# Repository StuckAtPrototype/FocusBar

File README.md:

# FocusBar

A compact Pomodoro timer device with visual LED progress bar, tactile button controls, and audio feedback. Designed to help you stay focused and productive.

## Features

- **Visual Progress Bar**: 10 WS2812 addressable RGB LEDs show timer progress
- **5 Preset Durations**: Quick-select buttons for 5, 15, 30, 45, and 60 minute focus sessions
- **Audio Feedback**: Piezo buzzer for startup jingle, completion notification, and alert sounds
- **Intuitive States**: Color-coded LED feedback for different timer states
- **USB-C Powered**: Modern, reversible connector for easy power
- **Compact Design**: Custom PCB with 3D-printable enclosure

## Timer States

| State | LED Color | Behavior |
|-------|-----------|----------|
| Idle | Cyan (30% brightness) | All LEDs solid, ready to start |
| Running | Green | Progress bar fills from 0-100% |
| Completed | Green (pulsing) | 60-second grace period to acknowledge |
| Alerting | Red (pulsing) | Audio alert every 2 seconds until dismissed |

## Usage

1. **Start Timer**: Press any of the 5 buttons to start the corresponding timer:
   - Button 1: 5 minutes
   - Button 2: 15 minutes
   - Button 3: 30 minutes
   - Button 4: 45 minutes
   - Button 5: 60 minutes

2. **Cancel Timer**: Press any button while timer is running to stop and reset

3. **Acknowledge Completion**: Press any button during the grace period (green pulsing) to reset without triggering the alert

4. **Dismiss Alert**: Press any button during the alert (red pulsing) to silence and reset

## Hardware

### Components

| Component | Part Number | Description |
|-----------|-------------|-------------|
| MCU | ESP32-H2-MINI-1 | WiFi/BLE microcontroller module |
| LEDs | IN-PI15TAT5R5G5B | WS2812-compatible addressable RGB LEDs (x10) |
| Buttons | TL1016AAF220QG | Tactile push buttons (x5) |
| Buzzer | SMT1240SHT | SMD piezo buzzer |
| Regulator | AP2205-33W5-7 | 3.3V LDO voltage regulator |
| USB | USB4105-GF-A | USB-C connector |
| ESD Protection | TPD1E10B06 | USB ESD protection diode |

### PCB

- **Design Tool**: KiCad
- **Files Location**: `hardware/`
- **Schematic**: `FocusBeam.kicad_sch`
- **PCB Layout**: `FocusBeam.kicad_pcb`
- **Gerbers**: `gerbers/` or `FocusBeam-v1.1-fab-gerbers.zip`
- **BOM**: `FocusBeam-v1.1-BOM.csv`
- **Panel Design**: `panel/` (for production runs)

### Mechanical

3D-printable enclosure files (STEP format) located in `mechanical/`:
- `FocusBeam_v1.1_front.step` - Front cover
- `FocusBeam_v1.1_back.step` - Back cover
- `FocusBeam_v1.1_buttons.step` - Button caps
- `FocusBeam_v.1.1_stand.step` - Desktop stand

## Firmware

### Requirements

- [ESP-IDF](https://docs.espressif.com/projects/esp-idf/en/latest/esp32h2/get-started/index.html) v5.x or later
- ESP32-H2 target support

### Building

```bash
cd firmware
idf.py set-target esp32h2
idf.py build
```

### Flashing

```bash
idf.py -p (PORT) flash monitor
```

Replace `(PORT)` with your serial port (e.g., `COM3` on Windows, `/dev/ttyUSB0` on Linux).

### Firmware Architecture

```
firmware/
├── CMakeLists.txt          # Project build configuration
├── sdkconfig.ci            # SDK configuration
└── main/
    ├── main.c              # Application entry point and main loop
    ├── button.c/h          # Button input handling (short/long press)
    ├── led.c/h             # LED control (colors, progress, pulsing)
    ├── led_color_lib.c/h   # Color utilities
    ├── piezo.c/h           # Buzzer control (tones, melodies)
    ├── timer.c/h           # Pomodoro state machine
    ├── serial_protocol.c/h # Serial communication (future use)
    └── ws2812_control.c/h  # WS2812 LED driver (RMT peripheral)
```

### Key Modules

- **Timer**: State machine managing idle, running, completed, grace period, and alerting states
- **LED**: Thread-safe LED control with smooth transitions and pulsing effects
- **Button**: Interrupt-driven button handler with debouncing and short/long press detection
- **Piezo**: PWM-based buzzer control for tones and melodies

## Pin Configuration

| Function | GPIO |
|----------|------|
| WS2812 Data | (see ws2812_control.c) |
| Button SW0 | GPIO 10 |
| Button SW1 | GPIO 5 |
| Button SW2 | GPIO 4 |
| Button SW3 | GPIO 14 |
| Button SW4 | GPIO 13 |
| Piezo | GPIO 22 |

## Project Structure

```
FocusBar/
├── README.md               # This file
├── firmware/               # ESP-IDF firmware project
│   ├── main/               # Source code
│   └── CMakeLists.txt
├── hardware/               # KiCad PCB design files
│   ├── FocusBeam.kicad_*   # Main PCB files
│   ├── gerbers/            # Manufacturing files
│   ├── panel/              # Panelized PCB for production
│   └── FocusBeam.step      # 3D model of PCB
└── mechanical/             # 3D-printable enclosure (STEP files)
```

## License

Licensed under the Apache License, Version 2.0. See [LICENSE](LICENSE) for details.

## Author

StuckAtPrototype, LLC

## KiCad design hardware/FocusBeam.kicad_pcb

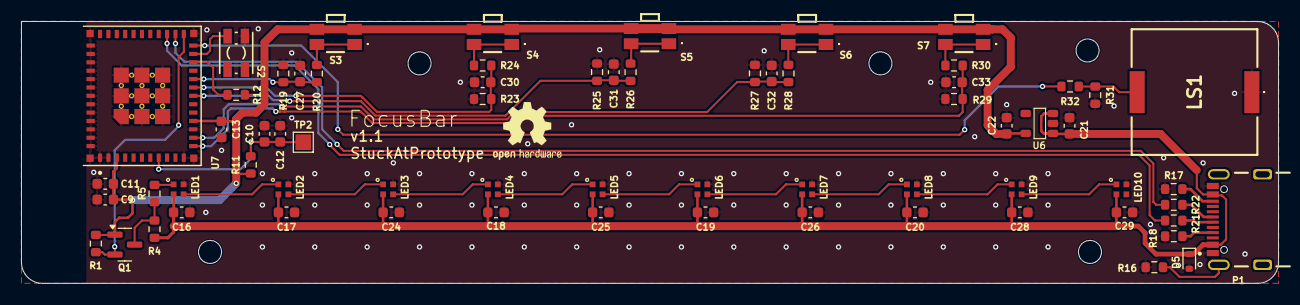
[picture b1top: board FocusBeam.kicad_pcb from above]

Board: 2 copper layers, 120.0 x 25.0 mm, 67 parts (0 on the bottom side), 37 nets.

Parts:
C9: 47uF; C_0603_1608Metric
C10: 1uF; C_0603_1608Metric
C11, C12, C13, C16, C17, C18, C19, C20, C24, C25, C26, C27, C28, C29, C30, C31, C32, C33: 0.1uF; C_0603_1608Metric
C21, C22: 10uF; C_0603_1608Metric
D5: TPD1E10B06; D_SOD-523
LED1, LED2, LED3, LED4, LED5, LED6, LED7, LED8, LED9, LED10: IN-PI15TAT5R5G5B; IN-PI15_INL
LS1: SMT1240SHT
P1: USB_C_Plug_USB2.0; GCT_USB4105-GF-A
Q1: BSS138; SOT-23
R1, R4, R11, R12: 10K; R_0603_1608Metric
R5: 470; R_0603_1608Metric
R16, R31: 1M; R_0603_1608Metric
R17, R18: 5K1; R_0603_1608Metric
R19, R23, R25, R27, R29: 100k; R_0603_1608Metric
R20, R24, R26, R28, R30: 10k; R_0603_1608Metric
R21, R22: 22; R_0603_1608Metric
R32: 100; R_0603_1608Metric
S2: SWITCH_0SMTRLFS
S3, S4, S5, S6, S7: TL1016AAF220QG
TP2: TestPoint; TestPoint_Pad_1.5x1.5mm
U6: AP2205; AP2204
U7: ESP32-H2-MINI-1; MODULE_ESP32-H2-MINI-1-H2

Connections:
+3V3: C9.1, C11.1, C13.1, C22.1, Q1.1 (G), R1.2, R11.1, R12.2, S3.3, S3.4, S4.3, S4.4, S5.3, S5.4, S6.3, S6.4, S7.3, S7.4, U6.5 (VOUT), U7.3 (3v3), U7.15 (VBAT)
+5VD: C16.1, C17.1, C18.1, C19.1, C20.1, C21.1, C24.1, C25.1, C26.1, C28.1, C29.1, D5.1, LED1.2 (VDD), LED2.2 (VDD), LED3.2 (VDD), LED4.2 (VDD), LED5.2 (VDD), LED6.2 (VDD), LED7.2 (VDD), LED8.2 (VDD), LED9.2 (VDD), LED10.2 (VDD), P1.A4 (VBUS), P1.A9 (VBUS), R4.2, U6.1 (VIN), U6.3 (EN)
/CP_EN: C10.1, C12.1, R11.2, TP2.1, U7.8 (EN)
/SW_0: C27.1, R19.1, R20.1, U7.20 (IO10)
/SW_1: C30.1, R23.1, R24.1, U7.19 (IO5)
/SW_2: C31.1, R25.1, R26.1, U7.18 (IO4)
/SW_3: C32.1, R27.1, R28.1, U7.13 (IO14)
/SW_4: C33.1, R29.1, R30.1, U7.12 (IO13)
/USB_D+: R21.1, U7.27 (IO27)
/USB_D-: R22.2, U7.26 (IO26)
GND: C9.2, C10.2, C11.2, C12.2, C13.2, C16.2, C17.2, C18.2, C19.2, C20.2, C21.2, C22.2, C24.2, C25.2, C26.2, C27.2, C28.2, C29.2, C30.2, C31.2, C32.2, C33.2, D5.2, LED1.4 (GND), LED2.4 (GND), LED3.4 (GND), LED4.4 (GND), LED5.4 (GND), LED6.4 (GND), LED7.4 (GND), LED8.4 (GND), LED9.4 (GND), LED10.4 (GND), LS1.1, P1.A1 (GND), P1.A12 (GND), R16.2, R17.2, R18.2, R19.2, R23.2, R25.2, R27.2, R29.2, R31.2, S2.1, U6.2 (GND), U7.1 (GND), U7.2 (GND), U7.11 (GND), U7.14 (GND), U7.36 (GND), U7.37 (GND), U7.38 (GND), U7.39 (GND), U7.40 (GND), U7.41 (GND), U7.42 (GND), U7.43 (GND), U7.44 (GND), U7.45 (GND), U7.46 (GND), U7.47 (GND), U7.48 (GND), U7.49 (EPAD), U7.50 (GND), U7.51 (GND), U7.52 (GND), U7.53 (GND)
unnamed: LED1.1 (DIN), R5.2
unnamed: LED1.3 (DOUT), LED2.1 (DIN)
unnamed: LED2.3 (DOUT), LED3.1 (DIN)
unnamed: LED3.3 (DOUT), LED4.1 (DIN)
unnamed: LED4.3 (DOUT), LED5.1 (DIN)
unnamed: LED5.3 (DOUT), LED6.1 (DIN)
unnamed: LED6.3 (DOUT), LED7.1 (DIN)
unnamed: LED7.3 (DOUT), LED8.1 (DIN)
unnamed: LED8.3 (DOUT), LED9.1 (DIN)
unnamed: LED9.3 (DOUT), LED10.1 (DIN)
unnamed: LS1.2, R31.1, R32.1
unnamed: P1.A5 (CC), R18.1
unnamed: P1.A6 (D+), R21.2
unnamed: P1.A7 (D-), R22.1
unnamed: P1.S1 (SHIELD), R16.1
unnamed: P1.B5 (VCONN), R17.1
unnamed: Q1.3 (D), R4.1, R5.1
unnamed: Q1.2 (S), R1.1, U7.25 (IO25)
unnamed: R20.2, S3.1, S3.2
unnamed: R24.2, S4.1, S4.2
unnamed: R26.2, S5.1, S5.2
unnamed: R28.2, S6.1, S6.2
unnamed: R30.2, S7.1, S7.2
unnamed: R12.1, U7.22 (IO08)
unnamed: S2.2, U7.23 (IO9)
unnamed: R32.2, U7.24 (IO22)

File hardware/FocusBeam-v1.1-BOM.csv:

Id,Designator,Footprint,Quantity,Designation,Supplier and ref
1,"C32,C26,C28,C12,C19,C31,C20,C24,C16,C33,C17,C27,C11,C30,C13,C25,C18,C29",C_0603_1608Metric,18,0.1uF,CC0603KRX7R7BB104
2,R5,R_0603_1608Metric,1,470,ESR03EZPF4700
3,"R25,R29,R19,R23,R27",R_0603_1608Metric,5,100k,WR06X1003FTL
4,"LED2,LED3,LED9,LED8,LED1,LED6,LED4,LED7,LED5,LED10",IN-PI15_INL,10,IN-PI15TAT5R5G5B,IN-PI15TAT5R5G5B
5,"R20,R28,R26,R24,R30",R_0603_1608Metric,5,10k,WR06X103 JTL
6,"S4,S6,S3,S7,S5",TL1016AAF220QG,5,TL1016AAF220QG,TL1016AAF220QG
7,C10,C_0603_1608Metric,1,1uF,CC0603KRX5R8BB105
8,"R21,R22",R_0603_1608Metric,2,22,RC0603JR-0722RL
9,U7,MODULE_ESP32-H2-MINI-1-H2,1,ESP32-H2-MINI-1,ESP32-H2-MINI-1
10,U6,AP2204,1,AP2205,AP2205-33W5-7
11,Q1,SOT-23,1,BSS138,BSS138
12,C9,C_0603_1608Metric,1,47uF,GRM188C80E476ME05D
13,"R1,R12,R4,R11",R_0603_1608Metric,4,10K,WR06X103 JTL
14,"C22,C21",C_0603_1608Metric,2,10uF,GRM188R61A106ME69D
15,S2,SWITCH_0SMTRLFS,1,SWITCH_0SMTRLFS,TL1016AAF220QG
16,"R31,R16",R_0603_1608Metric,2,1M,RMCF0603FT1M00
17,"R18,R17",R_0603_1608Metric,2,5K1,RC0603FR-075K1L
18,LS1,SMT1240SHT,1,SMT1240SHT,SMT1240SHT
19,D5,D_SOD-523,1,TPD1E10B06,TPD1E10B06DYAR
20,P1,GCT_USB4105-GF-A,1,USB_C_Plug_USB2.0,USB4105-GF-A
21,R32,R_0603_1608Metric,1,0,CRCW06030000Z0EI

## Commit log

2025-11-30 initial working version
2025-11-30 smooth progress bar unwind and idle color
2025-11-30 adding gitignore
2026-02-03 adding kicad files
2026-02-03 adding mechanicals
2026-02-03 readme + licensE
